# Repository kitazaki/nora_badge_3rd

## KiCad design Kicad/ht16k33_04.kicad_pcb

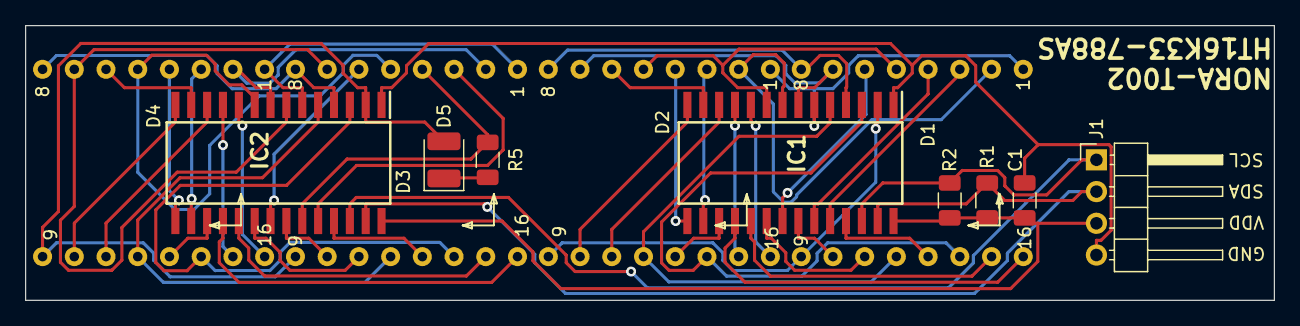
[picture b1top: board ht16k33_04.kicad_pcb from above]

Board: 2 copper layers, 100.0 x 22.0 mm, 12 parts (0 on the bottom side), 53 nets.

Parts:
C1: 10uF; C_1206_3216Metric
D1, D2, D3, D4: DISP_LED_MAT_8x8_COM_CAT; LED_8x8_1.9MM_20x20MM
D5: 1N4148; D_1210_3225Metric_Pad1.42x2.65mm_HandSolder
IC1, IC2: HT16K33-28SOP; SOIC127P1031X264-28N
J1: Conn_01x04_Male; PinHeader_1x04_P2.54mm_Horizontal
R1, R2, R5: 10K; R_1206_3216Metric

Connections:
GND: C1.2, IC1.1, IC2.1, J1.4
unnamed: D1.1, D2.1, IC1.6
unnamed: D1.2, D2.2, IC1.8
unnamed: D1.3, IC1.24
unnamed: D1.4, IC1.23
unnamed: D1.5, D2.5, IC1.9
unnamed: D1.6, IC1.21
unnamed: D1.7, D2.7, IC1.7
unnamed: D1.8, D2.8, IC1.4
unnamed: D1.9, D2.9, IC1.2
unnamed: D1.10, IC1.22
unnamed: D1.11, IC1.20
unnamed: D1.12, D2.12, IC1.5
unnamed: D1.13, IC1.25
unnamed: D1.14, D2.14, IC1.3
unnamed: D1.15, IC1.19
unnamed: D1.16, IC1.18
unnamed: D2.3, IC1.16
unnamed: D2.4, IC1.15
unnamed: D2.6, IC1.13
unnamed: D2.10, IC1.14
unnamed: D2.11, IC1.12
unnamed: D2.13, IC1.17
unnamed: D2.15, IC1.11
unnamed: D2.16, IC1.10
unnamed: D3.1, D4.1, IC2.6
unnamed: D3.2, D4.2, IC2.8
unnamed: D3.3, IC2.24
unnamed: D3.4, IC2.23, R5.1
unnamed: D3.5, D4.5, IC2.9
unnamed: D3.6, IC2.21
unnamed: D3.7, D4.7, IC2.7
unnamed: D3.8, D4.8, IC2.4
unnamed: D3.9, D4.9, D5.2, IC2.2
unnamed: D3.10, IC2.22
unnamed: D3.11, IC2.20
unnamed: D3.12, D4.12, IC2.5
unnamed: D3.13, IC2.25
unnamed: D3.14, D4.14, IC2.3
unnamed: D3.15, IC2.19
unnamed: D3.16, IC2.18
unnamed: D4.3, IC2.16
unnamed: D4.4, IC2.15
unnamed: D4.6, IC2.13
unnamed: D4.10, IC2.14
unnamed: D4.11, IC2.12
unnamed: D4.13, IC2.17
unnamed: D4.15, IC2.11
unnamed: D4.16, IC2.10
unnamed: D5.1, R5.2
unnamed: IC1.26, IC2.26, J1.1, R2.2
unnamed: IC1.27, IC2.27, J1.2, R1.2
VDD: C1.1, IC1.28, IC2.28, J1.3, R1.1, R2.1
